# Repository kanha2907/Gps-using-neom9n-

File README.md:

# Gps-using-neom9n-
      Compact GPS breakout board based on the u-blox NEO-M9N module. Includes support circuitry for battery-backed operation, LEDs, and passives—designed for low-power embedded GPS applications.

# GPS_M Module – Compact GPS Breakout Board

> Compact GPS breakout board based on the **u-blox NEO-M9N** module. Includes support circuitry for battery-backed operation, LEDs, and passives—designed for low-power embedded GPS applications.

---

## 📦 Files Included

- `GPS_m_gerber/`: Full set of Gerber files for PCB manufacturing.
- `neom9n.csv`: Bill of Materials (BOM) with part references, values, and footprints.

## 🧩 Overview

- **GPS Chip:** u-blox NEO-M9N
- **Power Source:** Designed for coin cell MS621T-FL11E
- **Form Factor:** Compact dual-layer board
- **Ideal For:** GPS logging, time synchronization, compact embedded systems

## 🔩 Components Overview

| Reference     | Value                   | Footprint               | Quantity |
|---------------|-------------------------|--------------------------|----------|
| B1            | 6.8MM Coin Cell         | MS621T-FL11E             | 1        |
| C1            | 47pF Capacitor          | GRM1885C1H470JA01D       | 1        |
| C3–C6         | 1uF Capacitors          | GRM21BR61C105KA01L       | 4        |
| CR1           | 1N4148WX-TP Diode       | CR_SOD323_MCC            | 1        |
| D1, D4        | LEDs                    | WL-SMCW_0603             | 2        |
| ...           | *(See full BOM file)*   |                          |          |

> 💡 For the full list of components, refer to `neom9n.csv`.

## 🛠️ How to Use

1. **Order the PCB** using the Gerber files in the `GPS_m_gerber/` folder.
2. **Order parts** based on the BOM file `neom9n.csv`.
3. **Assemble the board** using standard SMD soldering practices.

## 📎 License

This hardware design is released under the [CERN-OHL-W v2](https://ohwr.org/project/cernohl/wikis/home) open hardware license.

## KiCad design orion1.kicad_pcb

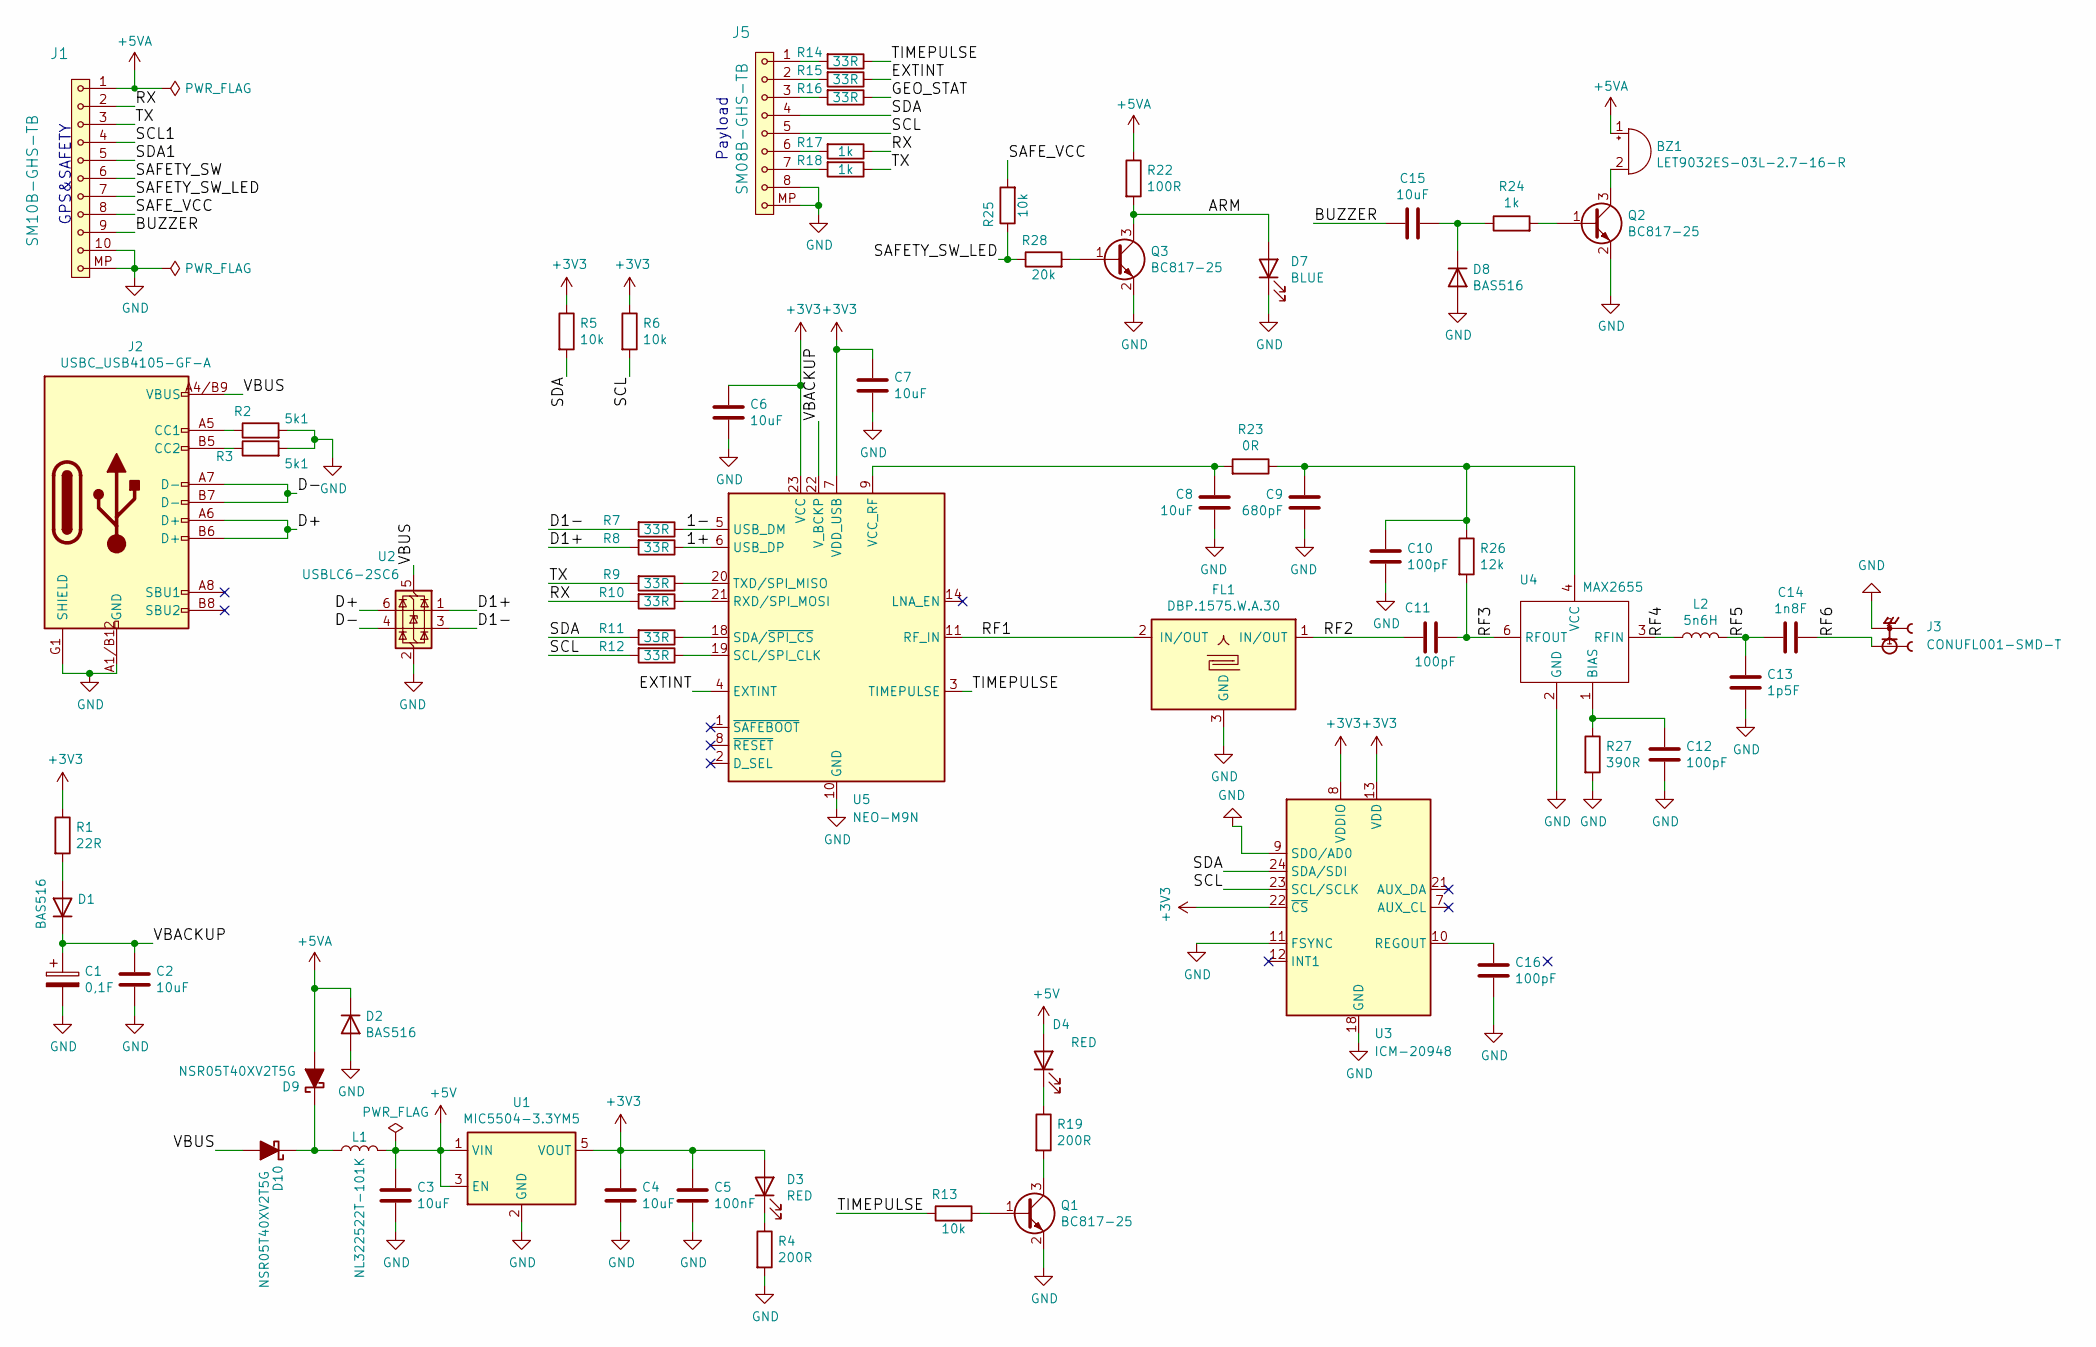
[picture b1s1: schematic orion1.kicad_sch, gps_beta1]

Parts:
BZ1: LET9032ES-03L-2.7-16-R; MagneticBuzzer_LET9032ES-03L-2.7-16-R
C1: 0,1F; CP_Elec_10x10.5
C2, C3, C4, C6, C7, C8, C15: 10uF; C_0805_2012Metric
C5: 100nF; C_0805_2012Metric
C9: 680pF; C_0805_2012Metric
C10, C11, C12, C16: 100pF; C_0805_2012Metric
C13: 1p5F; C_0805_2012Metric
C14: 1n8F; C_0805_2012Metric
D1, D2, D8: BAS516; D_SOD-523
D3, D4: RED; LED_1206_mill
D7: BLUE; LED_1206_mill
D9, D10: NSR05T40XV2T5G; D_SOD-523
FL1: DBP.1575.W.A.30; SAW DBP.1575.W.A.30
J1: SM10B-GHS-TB; JST_GH_SM10B-GHS-TB_1x10-1MP_P1.25mm_Horizontal
J2: USBC_USB4105-GF-A; USBC GCT_USB4105-GF-A
J3: CONUFL001-SMD-T; LINX_CONUFL001-SMD-T
J5: SM08B-GHS-TB; JST_GH_SM08B-GHS-TB_1x08-1MP_P1.25mm_Horizontal
L1: NL322522T-101K; L_1210_3225Metric
L2: 5n6H; L_0805_2012Metric
Q1, Q2, Q3: BC817-25; SOT-23
R1: 22R; R_0805_2012Metric
R2, R3: 5k1; R_0805_2012Metric
R4, R19: 200R; R_0805_2012Metric
R5, R6, R13, R25: 10k; R_0805_2012Metric
R7, R8, R9, R10, R11, R12, R14, R15, R16: 33R; R_0805_2012Metric
R17, R18, R24: 1k; R_0805_2012Metric
R22: 100R; R_0805_2012Metric
R23: 0R; R_0805_2012Metric
R26: 12k; R_0805_2012Metric
R27: 390R; R_0805_2012Metric
R28: 20k; R_0805_2012Metric
U1: MIC5504-3.3YM5; SOT-23-5
U2: USBLC6-2SC6; SOT-23-6
U3: ICM-20948; InvenSense_QFN-24_3x3mm_P0.4mm
U4: MAX2655; SOT-363_SC-70-6
U5: NEO-M9N; ublox_NEO

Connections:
+3V3: C4.1, C5.1, C6.1, C7.1, D3.2 (A), R1.1, R5.1, R6.1, U1.5 (VOUT), U3.8 (VDDIO), U3.13 (VDD), U3.22 (~CS), U5.7 (VDD_USB), U5.23 (VCC)
+5V: C3.1, D4.2 (A), L1.2, U1.1 (VIN), U1.3 (EN)
+5VA: BZ1.1 (+), D2.1 (K), D9.2 (A), J1.1, R22.1
/1+: R8.1, U5.6 (USB_DP)
/1-: R7.1, U5.5 (USB_DM)
/ARM: D7.2 (A), Q3.3 (C), R22.2
/BUZZER: C15.1, J1.9
/D1+: R8.2, U2.1 (I/O1)
/D1-: R7.2, U2.3 (I/O2)
/D+: J2.A6 (D+), J2.B6 (D+), U2.6 (I/O1)
/D-: J2.A7 (D-), J2.B7 (D-), U2.4 (I/O2)
/EXTINT: R15.1, U5.4 (EXTINT)
/GEO_STAT: R16.1; also elsewhere on the board
/RF1: FL1.2 (IN/OUT), U5.11 (RF_IN)
/RF2: C11.1, FL1.1 (IN/OUT)
/RF3: C11.2, R26.2, U4.6 (RFOUT)
/RF4: L2.1, U4.3 (RFIN)
/RF5: C13.2, C14.1, L2.2
/RF6: C14.2, J3.1
/RX: J1.2, R10.2, R17.1
/SAFETY_SW: J1.6
/SAFETY_SW_LED: J1.7, R25.1, R28.1
/SAFE_VCC: J1.8, R25.2
/SCL: J5.5, R6.2, R12.2, U3.23 (SCL/SCLK)
/SCL1: J1.4
/SDA: J5.4, R5.2, R11.2, U3.24 (SDA/SDI)
/SDA1: J1.5
/TIMEPULSE: R13.1, R14.1, U5.3 (TIMEPULSE)
/TX: J1.3, R9.2, R18.1
/VBACKUP: C1.1, C2.1, D1.1 (K), U5.22 (V_BCKP)
/VBUS: D10.2 (A), J2.A4/B9 (VBUS), J2.B4/A9 (VBUS), U2.5 (VBUS)
GND: C1.2, C2.2, C3.2, C4.2, C5.2, C6.2, C7.2, C8.2, C9.2, C10.2, C12.2, C13.1, C16.2, D2.2 (A), D7.1 (K), D8.2 (A), FL1.3 (GND), J1.10, J1.MP, J2.A1/B12 (GND), J2.B1/A12 (GND), J2.G1 (SHIELD), J2.G2 (SHIELD), J2.G3 (SHIELD), J2.G4 (SHIELD), J3.2, J3.3, J5.8, J5.MP, Q1.2 (E), Q2.2 (E), Q3.2 (E), R2.2, R3.2, R4.2, R27.2, U1.2 (GND), U2.2 (GND), U3.9 (SDO/AD0), U3.11 (FSYNC), U3.18 (GND), U3.20 (GND), U4.2 (GND), U4.5 (GND), U5.10 (GND), U5.12 (GND), U5.13 (GND), U5.24 (GND); also elsewhere on the board
unnamed: BZ1.2 (-), Q2.3 (C)
unnamed: D1.2 (A), R1.2
unnamed: D3.1 (K), R4.1
unnamed: D4.1 (K), R19.1
unnamed: C15.2, D8.1 (K), R24.1
unnamed: D9.1 (K), D10.1 (K), L1.1
unnamed: J2.A5 (CC1), R2.1
unnamed: J2.B5 (CC2), R3.1
unnamed: J5.1, R14.2
unnamed: J5.2, R15.2
unnamed: J5.3, R16.2
unnamed: J5.6, R17.2
unnamed: J5.7, R18.2
unnamed: Q1.1 (B), R13.2
unnamed: Q1.3 (C), R19.2
unnamed: Q2.1 (B), R24.2
unnamed: Q3.1 (B), R28.2
unnamed: C16.1, U3.10 (REGOUT)
unnamed: C12.1, R27.1, U4.1 (BIAS)
unnamed: C9.1, C10.1, R23.1, R26.1, U4.4 (VCC)
unnamed: R10.1, U5.21 (RXD/SPI_MOSI)
unnamed: R12.1, U5.19 (SCL/SPI_CLK)
unnamed: R11.1, U5.18 (SDA/~SPI_CS)
unnamed: R9.1, U5.20 (TXD/SPI_MISO)
unnamed: C8.1, R23.2, U5.9 (VCC_RF)

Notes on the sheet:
GPS&SAFETY
Payload

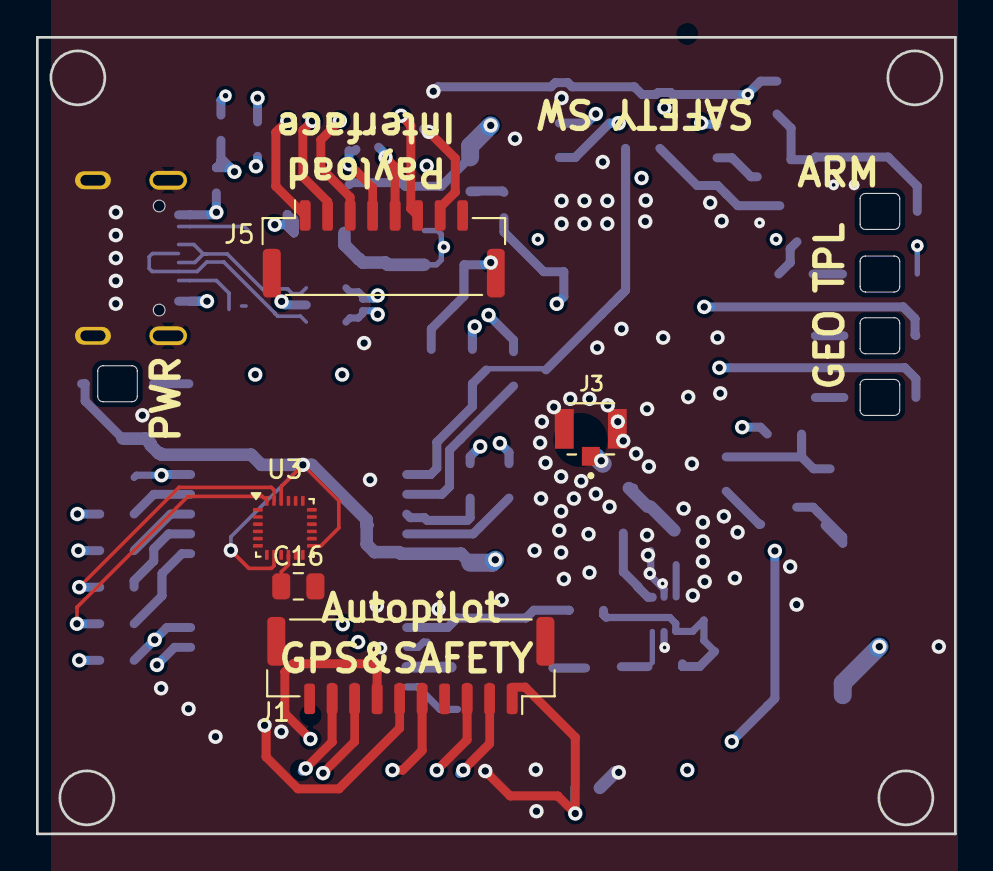
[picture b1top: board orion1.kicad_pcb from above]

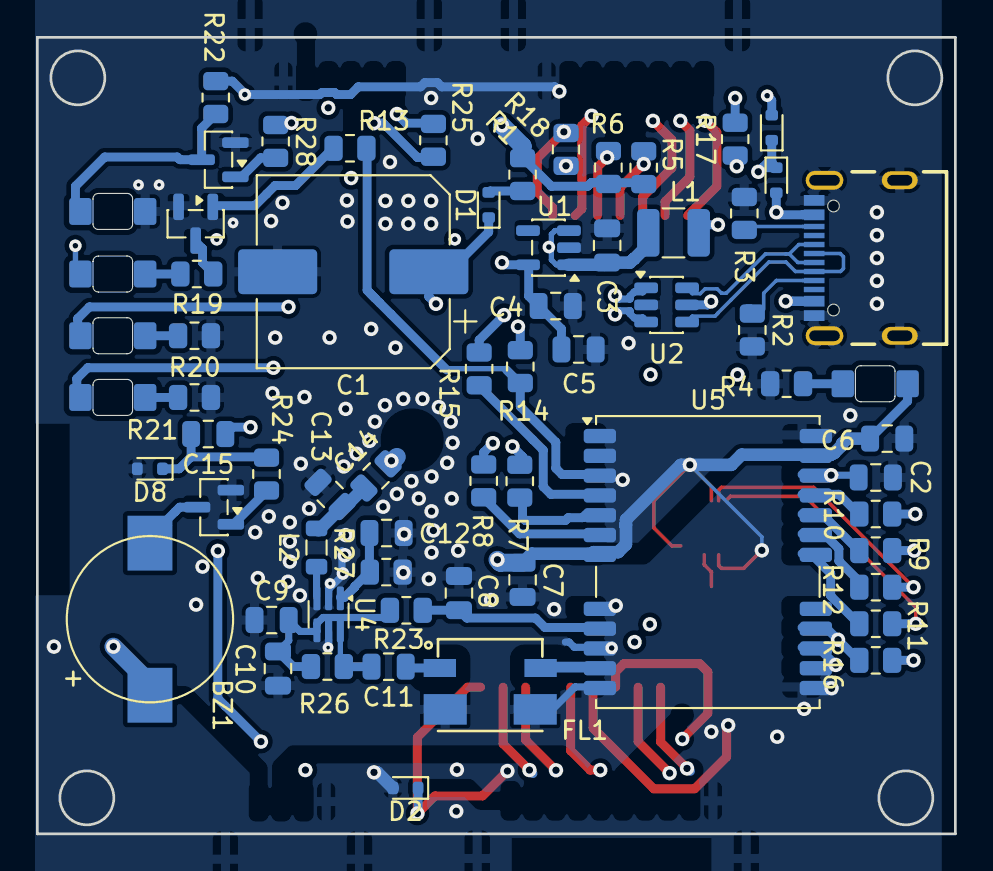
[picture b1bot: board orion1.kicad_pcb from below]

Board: 4 copper layers, 51.0 x 44.2 mm, 70 parts (65 on the bottom side), 56 nets.

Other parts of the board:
D5: YELLOW; LED_1206_mill
D6: GREEN; LED_1206_mill
R20, R21: 100R; R_0805_2012Metric

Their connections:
/GEO_STAT: D5.2 (A); also elsewhere on the board
GND: R20.2, R21.2; also elsewhere on the board
unnamed: D5.1 (K), R20.1
unnamed: D6.1 (K), R21.1

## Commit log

2026-06-14 Add files via upload
    Orion1 GNSS Navigation Module
    Overview
    Orion1 is a compact UAV navigation module designed for autonomous drones, robotics platforms, and precision navigation applications. The board integrates a high-performance multi-band GNSS receiver, 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
    The design is optimized for UAV flight controllers and supports RTK-capable navigation systems, making it suitable for mapping, surveying, precision agriculture, and autonomous vehicle applications.
    Key Features
    u-blox NEO-M9N multi-constellation GNSS receiver
